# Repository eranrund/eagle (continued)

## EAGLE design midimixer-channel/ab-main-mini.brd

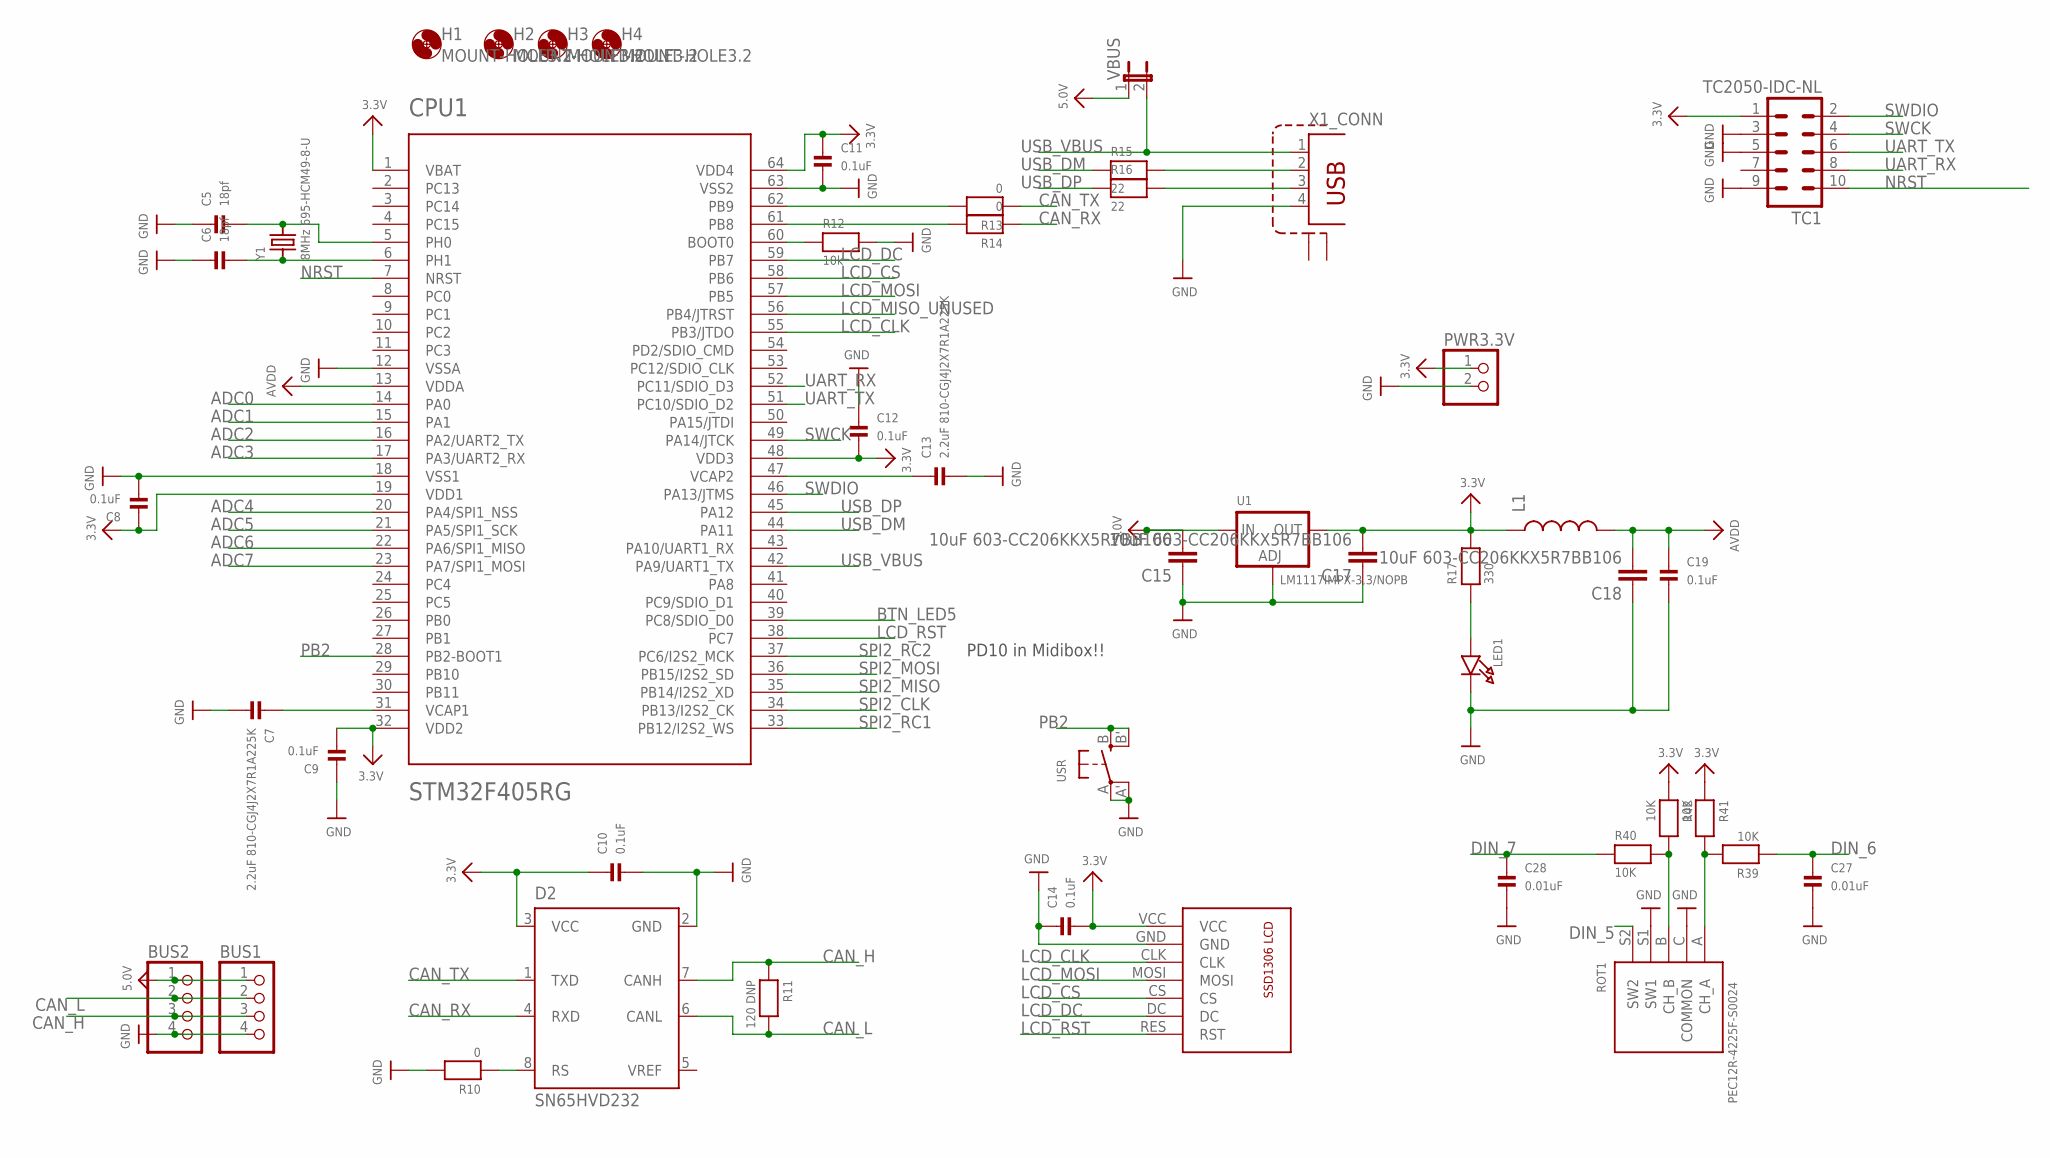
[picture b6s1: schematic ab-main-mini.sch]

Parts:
BUS1, BUS2: HEADER-1X4ROUND; 1X04_ROUND
C5, C6: 18pf; 0603
C7, C13: 2.2uF 810-CGJ4J2X7R1A225K; 0805
C8, C9, C10, C11, C12, C14, C19: 0.1uF; 0603
C15, C17, C18: 10uF 603-CC206KKX5R7BB106; 1206
C27, C28: 0.01uF; 0603
CPU1: STM32F405RG; TQFP64
D2: SN65HVD232; SO8
H1, H2, H3, H4: MOUNT-HOLE3.2; 3,2
L1: INDUCTOR0805; 0805
LED1: LED0603; CHIPLED_0603
PWR3.3V: HEADER-1X2ROUND; 1X02_ROUND
R10, R13, R14: 0; _0603
R11: 120 DNP; _0603
R12: 10k; _0603
R15, R16: 22; 0603
R17: 330; 0603
R39, R40, R41, R42: 10K; 0603
ROT1: PEC12R-4225F-S0024; PEC111-4XXXK-SXXXX
TC1: TC2050-IDC-NL
U1: LM1117IMPX-3.3/NOPB; SOT223-R
U$21: SSD1306-7PIN
USR: SWITCH_TACT_SMT; EVQ-Q2
VBUS: JUMPER2
X1: TE-292304-1
Y1: 8MHz 695-HCM49-8-U; HC49UP

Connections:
3.3V: C8.1, C9.2, C10.1, C11.1, C12.2, C14.2, C17.2, CPU1.1 (VBAT), CPU1.19 (VDD1), CPU1.32 (VDD2), CPU1.48 (VDD3), CPU1.64 (VDD4), D2.3 (VCC), L1.1, PWR3.3V.1, R17.2, R41.1, R42.1, TC1.1, U1.2 (OUT), U$21.VCC
5.0V: BUS1.1, BUS2.1, C15.2, U1.3 (IN), VBUS.1
ADC0: CPU1.14 (PA0)
ADC1: CPU1.15 (PA1)
ADC2: CPU1.16 (PA2/UART2_TX)
ADC3: CPU1.17 (PA3/UART2_RX)
ADC4: CPU1.20 (PA4/SPI1_NSS)
ADC5: CPU1.21 (PA5/SPI1_SCK)
ADC6: CPU1.22 (PA6/SPI1_MISO)
ADC7: CPU1.23 (PA7/SPI1_MOSI)
AVDD: C18.2, C19.1, CPU1.13 (VDDA), L1.2
BTN_LED5: CPU1.39 (PC8/SDIO_D0)
CAN_H: BUS1.3, BUS2.3, D2.7 (CANH), R11.1
CAN_L: BUS1.2, BUS2.2, D2.6 (CANL), R11.2
CAN_RX: D2.4 (RXD), R14.1
CAN_TX: D2.1 (TXD), R13.1
DIN_5: ROT1.S2 (SW2)
DIN_6: C27.1, R39.1
DIN_7: C28.1, R40.1
GND: BUS1.4, BUS2.4, C5.1, C6.1, C7.2, C8.2, C9.1, C10.2, C11.2, C12.1, C13.2, C14.1, C15.1, C17.1, C18.1, C19.2, C27.2, C28.2, CPU1.12 (VSSA), CPU1.18 (VSS1), CPU1.63 (VSS2), D2.2 (GND), LED1.C, PWR3.3V.2, R10.2, R12.2, ROT1.C (COMMON), ROT1.S1 (SW1), TC1.3, TC1.5, TC1.9, U1.1 (ADJ), U$21.GND, USR.A, USR.A' (P1), X1.4
LCD_CLK: CPU1.55 (PB3/JTDO), U$21.CLK
LCD_CS: CPU1.58 (PB6), U$21.CS
LCD_DC: CPU1.59 (PB7), U$21.DC
LCD_MISO_UNUSED: CPU1.56 (PB4/JTRST)
LCD_MOSI: CPU1.57 (PB5), U$21.MOSI
LCD_RST: CPU1.38 (PC7), U$21.RES (RST)
unnamed: C6.2, CPU1.6 (PH1), Y1.1
unnamed: C5.2, CPU1.5 (PH0), Y1.2
unnamed: C13.1, CPU1.47 (VCAP2)
unnamed: C7.1, CPU1.31 (VCAP1)
unnamed: LED1.A, R17.1
unnamed: CPU1.60 (BOOT0), R12.1
unnamed: R15.2, X1.2
unnamed: R16.2, X1.3
unnamed: CPU1.62 (PB9), R13.2
unnamed: CPU1.61 (PB8), R14.2
unnamed: R40.2, R42.2, ROT1.B (CH_B)
unnamed: R39.2, R41.2, ROT1.A (CH_A)
unnamed: D2.8 (RS), R10.1
NRST: CPU1.7 (NRST), TC1.10
PB2: CPU1.28 (PB2-BOOT1), USR.B (S), USR.B' (S1)
SPI2_CLK: CPU1.34 (PB13/I2S2_CK)
SPI2_MISO: CPU1.35 (PB14/I2S2_XD)
SPI2_MOSI: CPU1.36 (PB15/I2S2_SD)
SPI2_RC1: CPU1.33 (PB12/I2S2_WS)
SPI2_RC2: CPU1.37 (PC6/I2S2_MCK)
SWCK: CPU1.49 (PA14/JTCK), TC1.4
SWDIO: CPU1.46 (PA13/JTMS), TC1.2
UART_RX: CPU1.52 (PC11/SDIO_D3), TC1.8
UART_TX: CPU1.51 (PC10/SDIO_D2), TC1.6
USB_DM: CPU1.44 (PA11), R15.1
USB_DP: CPU1.45 (PA12), R16.1
USB_VBUS: CPU1.42 (PA9/UART1_TX), VBUS.2, X1.1

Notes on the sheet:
PD10 in Midibox!!

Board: 2 copper layers, 47 parts (33 on the bottom side), 37 nets, no tracks yet.

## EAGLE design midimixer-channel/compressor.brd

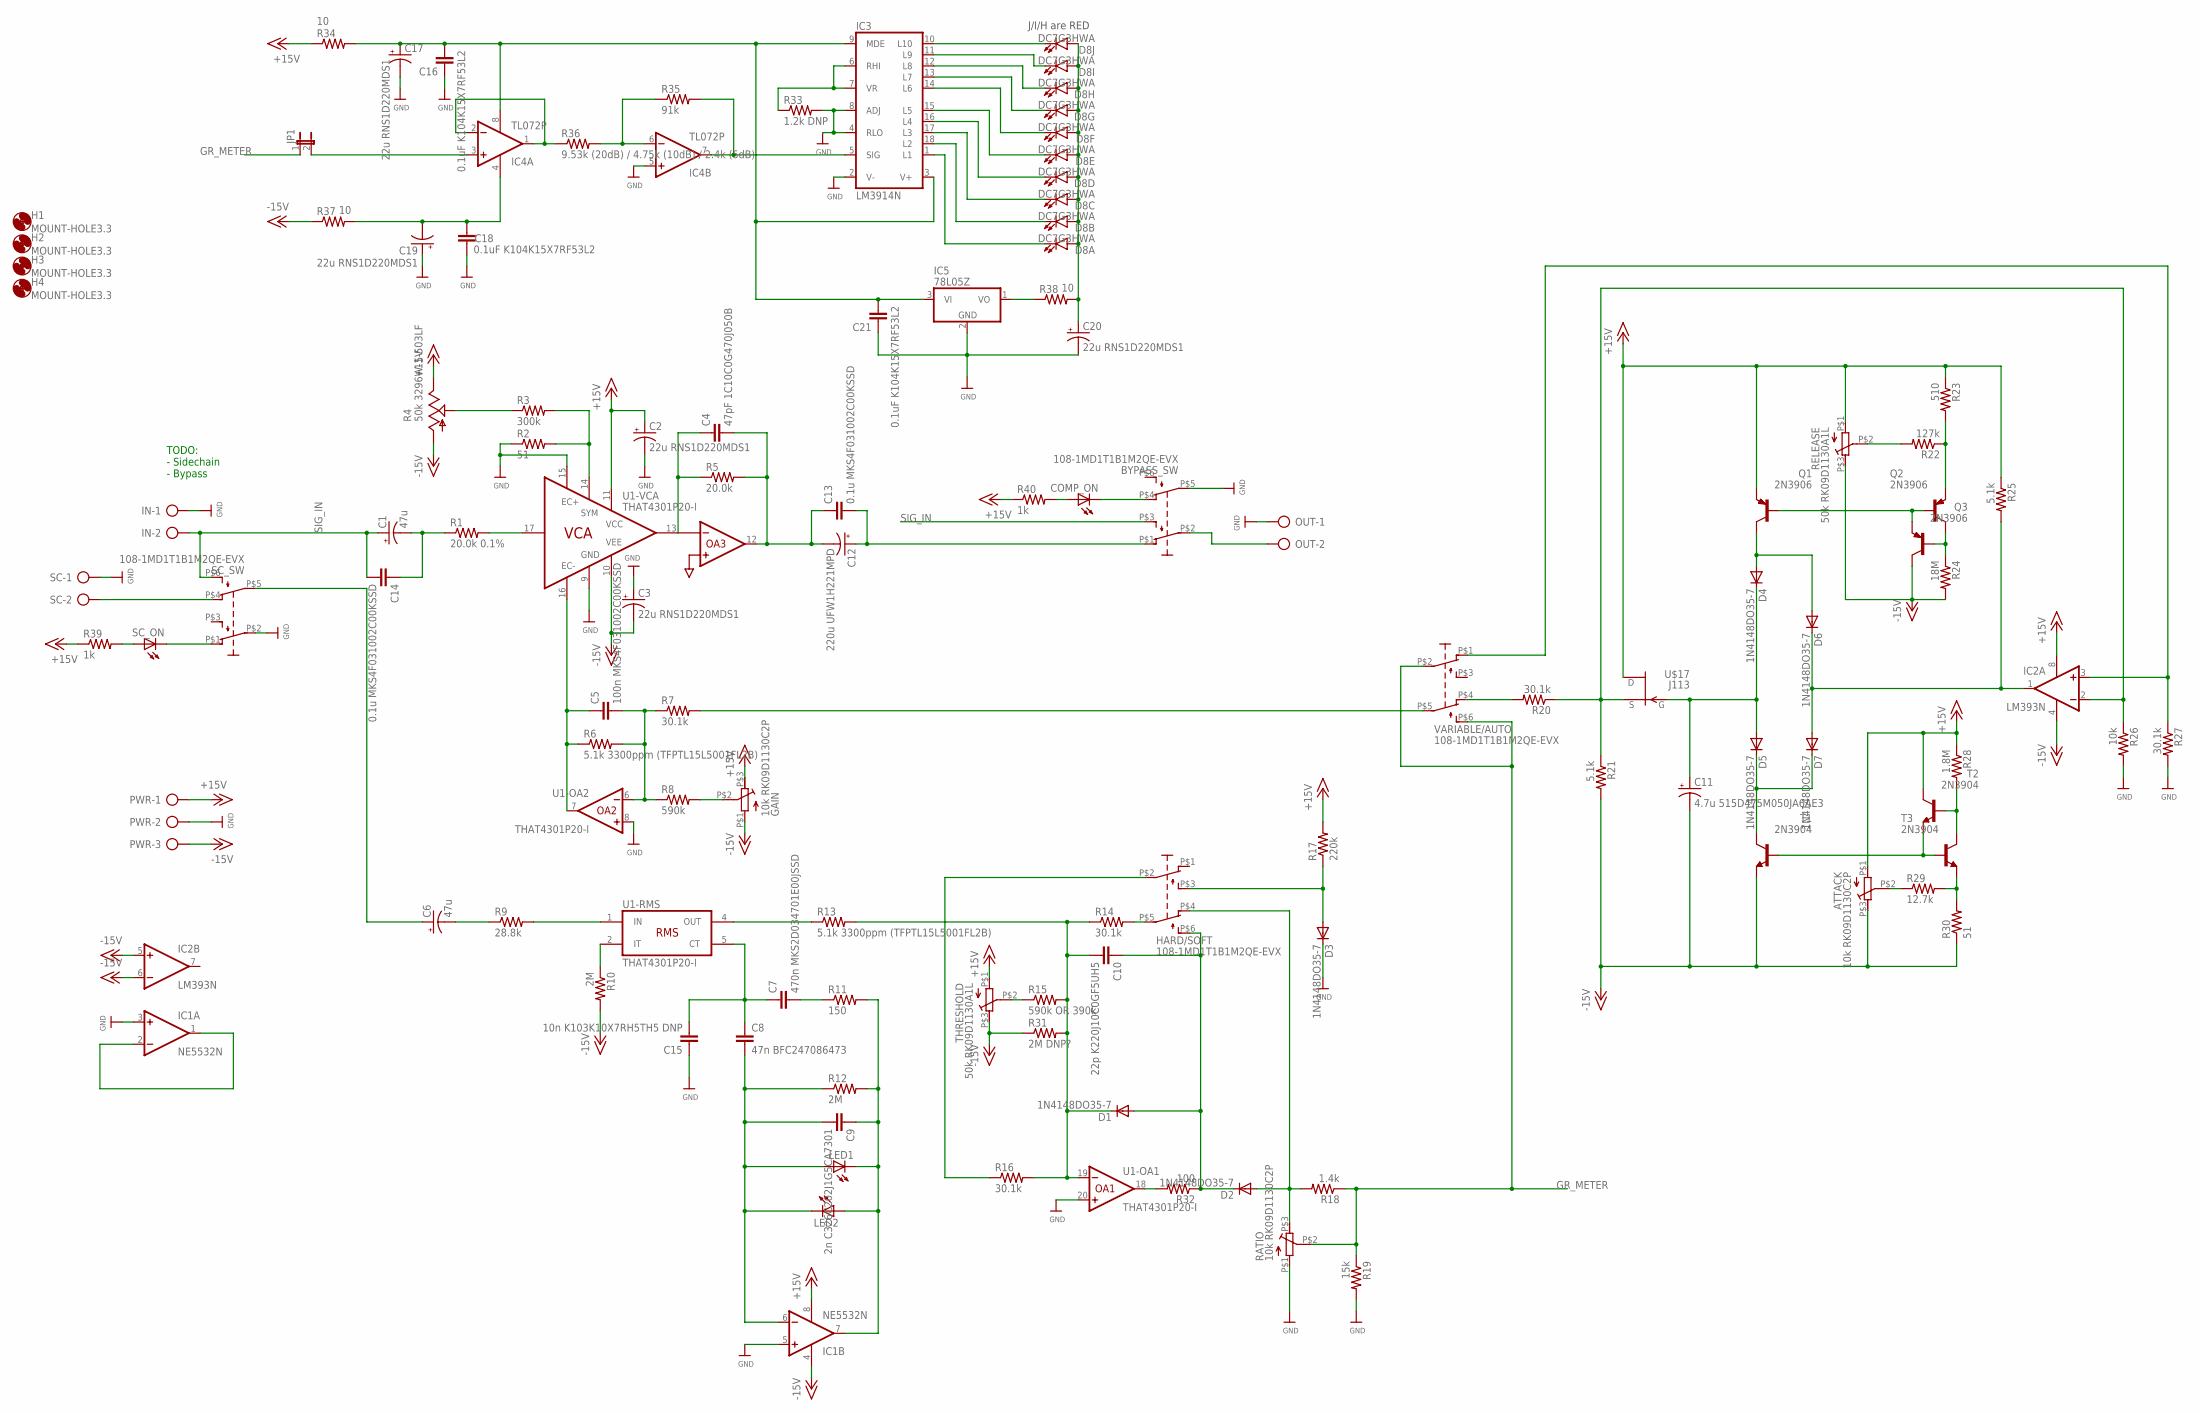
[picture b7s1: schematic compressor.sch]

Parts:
ATTACK: 10k RK09D1130C2P; ALPS-RK09D1130
BYPASS_SW: 108-1MD1T1B1M2QE-EVX
C1: 47u; B45181D
C2, C3, C17, C19, C20: 22u RNS1D220MDS1; E2,5-7
C4: 47pF 1C10C0G470J050B; C025-060X050
C5: 100n MKS4F031002C00KSSD; C7.5B4
C6: 47u; B45181D; MPN ERJ-1TRQFR47U
C7: 470n MKS2D034701E00JSSD; C5B4.5
C8: 47n BFC247086473; C5B7.2
C9: 2n C326C202J1G5CA7301; C5B2.5
C10: 22p K220J10C0GF5UH5; C050-035X075
C11: 4.7u 515D475M050JA6AE3; E2-5
C12: 220u UFW1H221MPD; E5-10,5
C13, C14: 0.1u MKS4F031002C00KSSD; C7.5B4
C15: 10n K103K10X7RH5TH5 DNP; C050-025X075
C16, C18, C21: 0.1uF K104K15X7RF53L2; C025-024X044
COMP_ON: LED5MM
D1, D2, D3, D4, D5, D6, D7: 1N4148DO35-7; DO35-7
D8: DC7G3HWA; LED_BARGAPH_10
GAIN: 10k RK09D1130C2P; ALPS-RK09D1130
H1, H2, H3, H4: MOUNT-HOLE3.3; 3,3
HARD/SOFT: 108-1MD1T1B1M2QE-EVX
IC1: NE5532N; DIL08
IC2: LM393N; DIL08
IC3: LM3914N; DIL18
IC4: TL072P; DIL08
IC5: 78L05Z; TO92
IN: AK500/2
JP1: JP1E; JP1
LED1, LED2: LED5MM
OUT: AK500/2
PWR: AK500/3
Q1, Q2, Q3: 2N3906; TO92
R1: 20.0k 0.1%; 0204/7
R2, R30: 51; 0204/7
R3: 300k; 0204/7
R4: 50k 3296W-1-503LF; S64W
R5: 20.0k; 0204/7
R6, R13: 5.1k 3300ppm (TFPTL15L5001FL2B); 0204/7
R7, R14, R16, R20, R27: 30.1k; 0204/7
R8: 590k; 0204/7
R9: 28.8k; 0204/7
R10, R12: 2M; 0204/7
R11: 150; 0204/7
R15: 590k OR 390k; 0204/7
R17: 220k; 0204/7
R18: 1.4k; 0204/7
R19: 15k; 0204/7
R21, R25: 5.1k; 0204/7
R22: 127k; 0204/7
R23: 510; 0204/7
R24: 18M; 0204/7
R26: 10k; 0204/7
R28: 1.8M; 0204/7
R29: 12.7k; 0204/7
R31: 2M DNP?; 0204/7
R32: 100; 0204/7
R33: 1.2k DNP; 0204/7
R34, R37, R38: 10; 0204/7
R35: 91k; 0204/7
R36: 9.53k (20dB) / 4.75k (10dB) / 2.4k (5dB); 0204/7
R39, R40: 1k; 0204/7
RATIO: 10k RK09D1130C2P; ALPS-RK09D1130
RELEASE: 50k RK09D1130A1L; ALPS-RK09D1130
SC: AK500/2
SC_ON: LED5MM
SC_SW: 108-1MD1T1B1M2QE-EVX
T1, T2, T3: 2N3904; TO92
THRESHOLD: 50k RK09D1130A1L; ALPS-RK09D1130
U1: THAT4301P20-I; DIL20
U$17: J113; J113-TO92
VARIABLE/AUTO: 108-1MD1T1B1M2QE-EVX

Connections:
+15V: ATTACK.P$1 (E), C2.+, GAIN.P$3 (A), IC1.8 (V+), IC2.8 (V+), PWR.1, Q1.3 (E), R4.E, R17.2, R23.1, R25.1, R28.1, R34.1, R39.1, R40.1, RELEASE.P$1 (E), T2.1 (C), THRESHOLD.P$1 (E), U1.11 (VCC), U$17.D
-15V: ATTACK.P$3 (A), C3.-, C11.-, GAIN.P$1 (E), IC1.4 (V-), IC2.4 (V-), IC2.5 (+IN), IC2.6 (-IN), PWR.3, Q3.1 (C), R4.A, R10.2, R21.2, R24.2, R30.1, R31.1, R37.1, RELEASE.P$3 (A), T1.3 (E), THRESHOLD.P$3 (A), U1.10 (VEE)
GND: BYPASS_SW.P$5 (P1), C2.-, C3.+, C15.1, C16.1, C17.-, C18.1, C19.+, C20.-, C21.1, D3.C, IC1.3 (+IN), IC1.5 (+IN), IC3.2 (V-), IC3.4 (RLO), IC3.8 (ADJ), IC4.5 (+IN), IC5.2 (GND), IN.1, OUT.1, PWR.2, R2.1, R19.2, R26.2, R27.2, R33.2, RATIO.P$1 (E), SC.1, SC_SW.P$2, U1.8 (+IN), U1.9 (GND), U1.15 (EC+), U1.20 (+IN)
GR_METER: JP1.1, R18.1, R19.1, RATIO.P$2 (S), VARIABLE/AUTO.P$2, VARIABLE/AUTO.P$6 (S1)
unnamed: SC.2, SC_SW.P$4 (O1)
unnamed: C1.-, C14.1, R1.1
unnamed: R1.2, U1.17 (IN)
unnamed: R3.1, R4.S
unnamed: C4.2, C12.-, C13.1, R5.2, U1.12 (OA3_OUT)
unnamed: R2.2, R3.2, U1.14 (SYM)
unnamed: C4.1, R5.1, U1.13 (VCA_OUT)
unnamed: C5.1, R6.1, U1.7 (OUT), U1.16 (EC-)
unnamed: C5.2, R6.2, R7.1, R8.1, U1.6 (-IN)
unnamed: IC5.1 (VO), R38.1
unnamed: GAIN.P$2 (S), R8.2
unnamed: R13.1, U1.4 (RMS-OUT)
unnamed: C6.-, R9.1
unnamed: R9.2, U1.1 (RMS-IN)
unnamed: R10.1, U1.2 (RMS-IT)
unnamed: C7.2, R11.1
unnamed: C7.1, C8.1, C15.2, U1.5 (RMS-CT)
unnamed: C9.1, IC1.7 (OUT), LED1.K (C), LED2.A, R11.2, R12.2
unnamed: C8.2, C9.2, IC1.6 (-IN), LED1.A, LED2.K (C), R12.1
unnamed: C10.2, D1.C, R13.2, R14.1, R15.2, R16.2, R31.2, U1.19 (-IN)
unnamed: R15.1, THRESHOLD.P$2 (S)
unnamed: HARD/SOFT.P$5 (P1), R14.2
unnamed: C10.1, D1.A, D2.C, HARD/SOFT.P$6 (S1), R32.1
unnamed: D2.A, HARD/SOFT.P$4 (O1), R18.2, RATIO.P$3 (A)
unnamed: HARD/SOFT.P$2, R16.1
unnamed: D3.A, HARD/SOFT.P$3 (S), R17.1
unnamed: IC2.2 (-IN), R20.1, R21.1, R26.1, U$17.S
unnamed: SC_ON.K (C), SC_SW.P$1 (O)
unnamed: R20.2, VARIABLE/AUTO.P$4 (O1)
unnamed: IC2.3 (+IN), R27.1, VARIABLE/AUTO.P$1 (O)
unnamed: C11.+, D4.C, D5.A, U$17.G
unnamed: D5.C, D7.C, T1.1 (C)
unnamed: D4.A, D6.A, Q1.1 (C)
unnamed: R22.2, RELEASE.P$2 (S)
unnamed: D6.C, D7.A, IC2.1 (OUT), R25.2
unnamed: Q2.3 (E), R22.1, R23.2
unnamed: Q1.2 (B), Q2.2 (B), Q3.3 (E)
unnamed: Q2.1 (C), Q3.2 (B), R24.1
unnamed: T1.2 (B), T2.3 (E), T3.2 (B)
unnamed: R28.2, T2.2 (B), T3.1 (C)
unnamed: BYPASS_SW.P$1 (O), C12.+, C13.2
unnamed: R32.2, U1.18 (OUT)
unnamed: D8.11 (C), IC3.10 (L10)
unnamed: ATTACK.P$2 (S), R29.1
unnamed: R29.2, R30.2, T3.3 (E)
unnamed: D8.12 (C), IC3.11 (L9)
unnamed: D8.13 (C), IC3.12 (L8)
unnamed: D8.14 (C), IC3.13 (L7)
unnamed: D8.15 (C), IC3.14 (L6)
unnamed: D8.16 (C), IC3.15 (L5)
unnamed: D8.17 (C), IC3.16 (L4)
unnamed: D8.18 (C), IC3.17 (L3)
unnamed: D8.19 (C), IC3.18 (L2)
unnamed: D8.20 (C), IC3.1 (L1)
unnamed: IC3.6 (RHI), IC3.7 (VR), R33.1
unnamed: R39.2, SC_ON.A
unnamed: BYPASS_SW.P$2, OUT.2
unnamed: IC3.5 (SIG), IC4.7 (OUT), R35.2
unnamed: IC4.6 (-IN), R35.1, R36.2
unnamed: IC4.1 (OUT), IC4.2 (-IN), R36.1
unnamed: C18.2, C19.-, IC4.4 (V-), R37.2
unnamed: C20.+, D8.1 (A), D8.2 (A), D8.3 (A), D8.4 (A), D8.5 (A), D8.6 (A), D8.7 (A), D8.8 (A), D8.9 (A), D8.10 (A), R38.2
unnamed: C16.2, C17.+, C21.2, IC3.3 (V+), IC3.9 (MDE), IC4.8 (V+), IC5.3 (VI), R34.2
unnamed: BYPASS_SW.P$4 (O1), COMP_ON.K (C)
unnamed: COMP_ON.A, R40.2
unnamed: R7.2, VARIABLE/AUTO.P$5 (P1)
unnamed: IC4.3 (+IN), JP1.2
unnamed: IC1.1 (OUT), IC1.2 (-IN)
SC_IN: C6.+, SC_SW.P$5 (P1)
SIG_IN: BYPASS_SW.P$3 (S), C1.+, C14.2, IN.2, SC_SW.P$6 (S1)

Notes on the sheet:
TODO: - Sidechain - Bypass
J/I/H are RED

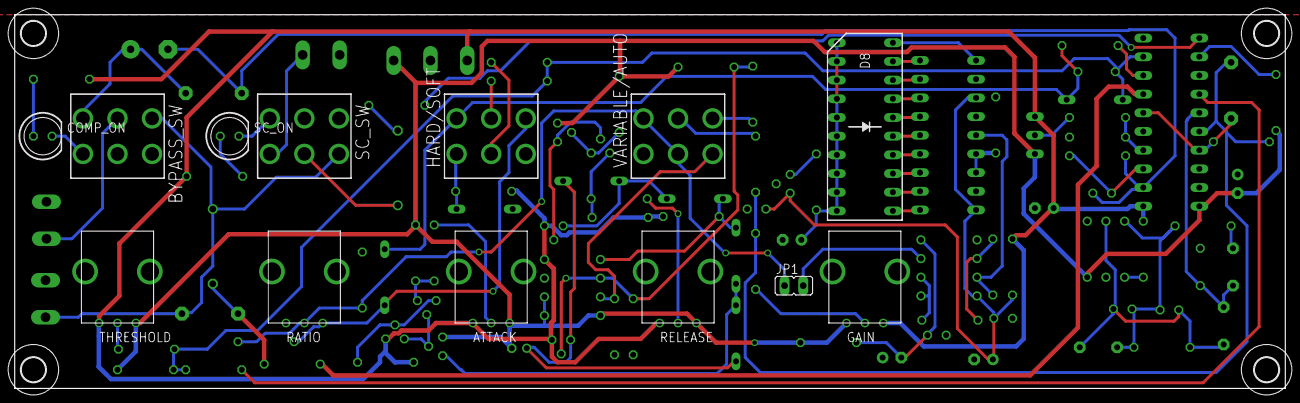
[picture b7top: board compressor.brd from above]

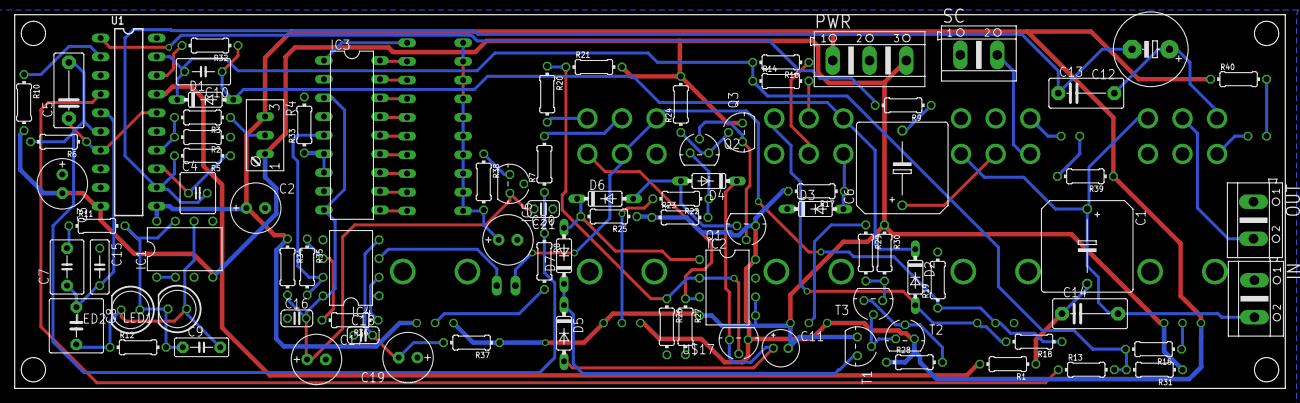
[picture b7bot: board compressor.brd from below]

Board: 2 copper layers, 172.7 x 50.8 mm, 104 parts (87 on the bottom side), 74 nets.

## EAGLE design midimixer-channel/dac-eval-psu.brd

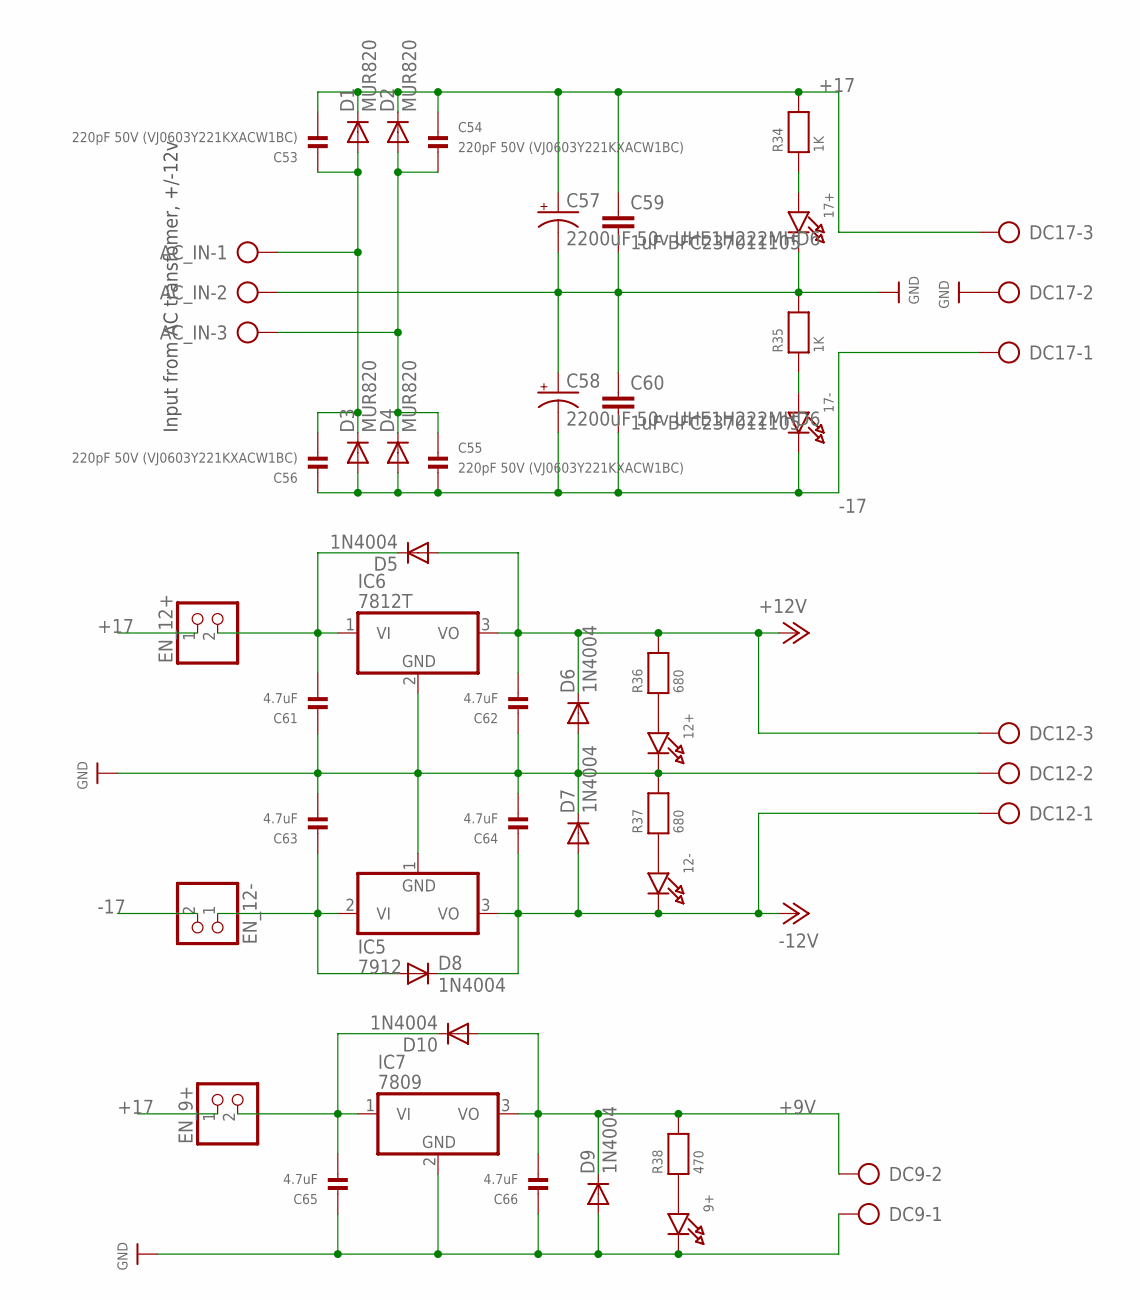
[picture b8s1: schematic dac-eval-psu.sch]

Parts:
9+, 12+, 12-, 17+, 17-: LED0603; CHIPLED_0603
AC_IN: AK500/3
C53, C54, C55, C56: 220pF 50V (VJ0603Y221KXACW1BC); 0603
C57, C58: 2200uF 50v UHE1H222MHD6; E7,5-18
C59, C60: 1uF BFC237011105; C5B7.2
C61, C62, C63, C64, C65, C66: 4.7uF; 0603
D1, D2, D3, D4: MUR820; C221B1A
D5, D6, D7, D8, D9, D10: 1N4004; DO41-10
DC9: AK500/2
DC12, DC17: AK500/3
EN_9+, EN_12+, EN_12-: HEADER-1X2ROUND; 1X02_ROUND
IC5: 7912; TO220H
IC6: 7812T; TO220H
IC7: 7809; TO220H
R34, R35: 1K; 0603
R36, R37: 680; 0603
R38: 470; 0603

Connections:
+9V: C66.2, D9.C, D10.A, DC9.2, IC7.3 (VO), R38.2
+12V: C62.2, D5.A, D6.C, DC12.3, IC6.3 (VO), R36.2
+17: C53.2, C54.1, C57.+, C59.1, D1.C, D2.C, DC17.3, EN_9+.1, EN_12+.1, R34.2
-12V: 12-.C, C64.1, D7.A, D8.C, DC12.1, IC5.3 (VO)
-17: 17-.C, C55.2, C56.1, C58.-, C60.2, D3.A, D4.A, DC17.1, EN_12-.2
GND: 9+.C, 12+.C, 17+.C, AC_IN.2, C57.-, C58.+, C59.2, C60.1, C61.1, C62.1, C63.2, C64.2, C65.1, C66.1, D6.A, D7.C, D9.A, DC9.1, DC12.2, DC17.2, IC5.1 (GND), IC6.2 (GND), IC7.2 (GND), R35.2, R37.2
unnamed: C65.2, D10.C, EN_9+.2, IC7.1 (VI)
unnamed: AC_IN.1, C53.1, C56.2, D1.A, D3.C
unnamed: AC_IN.3, C54.2, C55.1, D2.A, D4.C
unnamed: 17-.A, R35.1
unnamed: 17+.A, R34.1
unnamed: C61.2, D5.C, EN_12+.2, IC6.1 (VI)
unnamed: C63.1, D8.A, EN_12-.1, IC5.2 (VI)
unnamed: 9+.A, R38.1
unnamed: 12+.A, R36.1
unnamed: 12-.A, R37.1

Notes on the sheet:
Input from AC transfomer, +/-12v

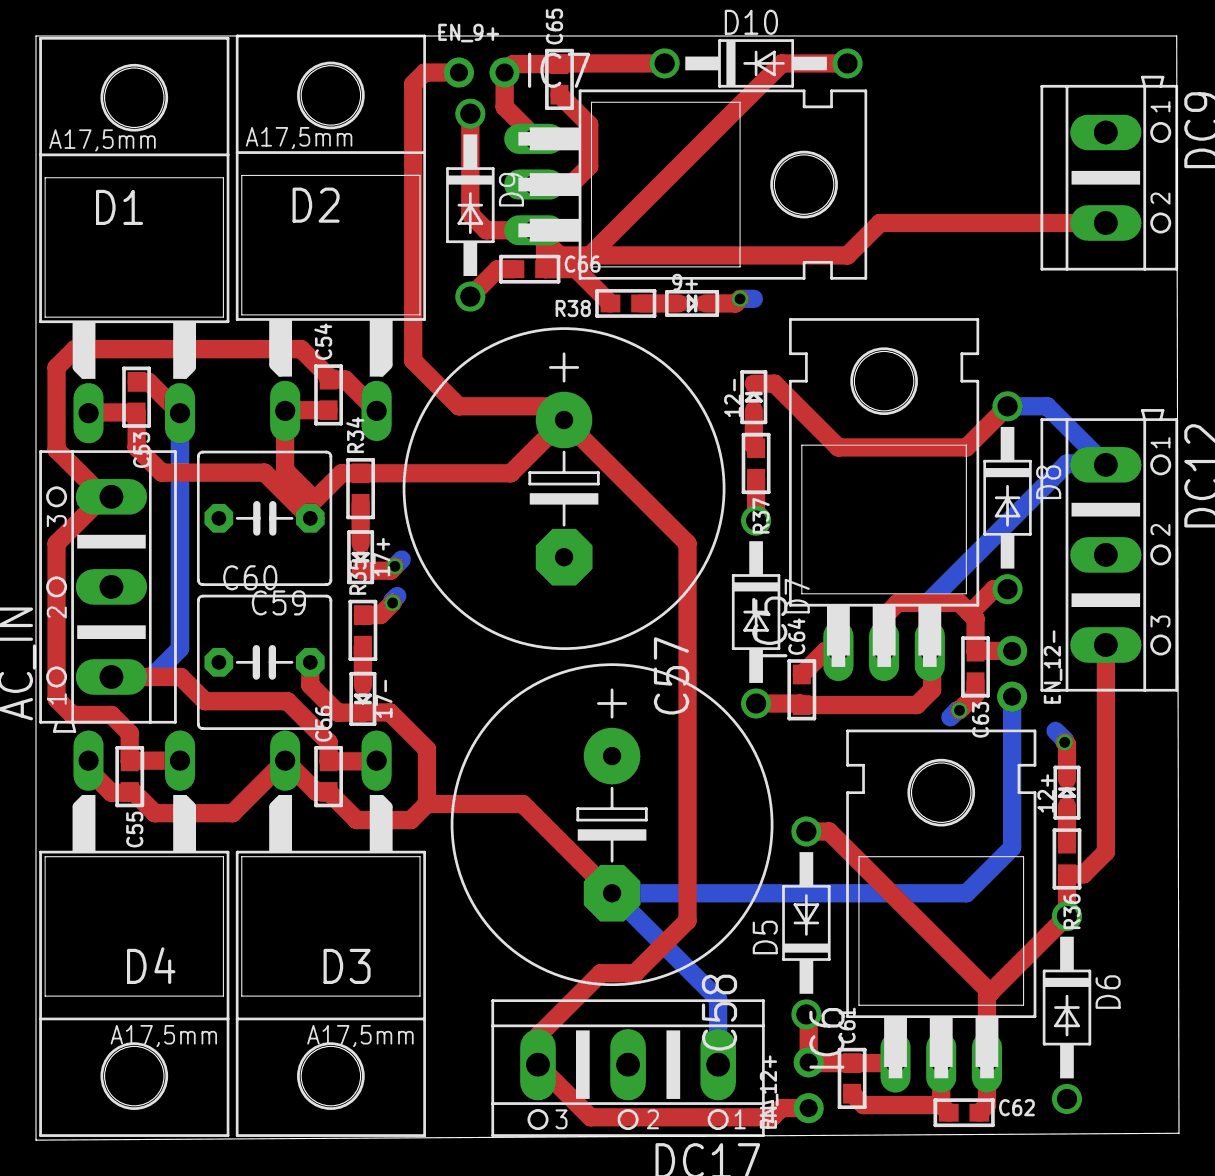
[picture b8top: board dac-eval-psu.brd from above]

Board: 2 copper layers, 63.5 x 61.3 mm, 44 parts (0 on the bottom side), 16 nets.
